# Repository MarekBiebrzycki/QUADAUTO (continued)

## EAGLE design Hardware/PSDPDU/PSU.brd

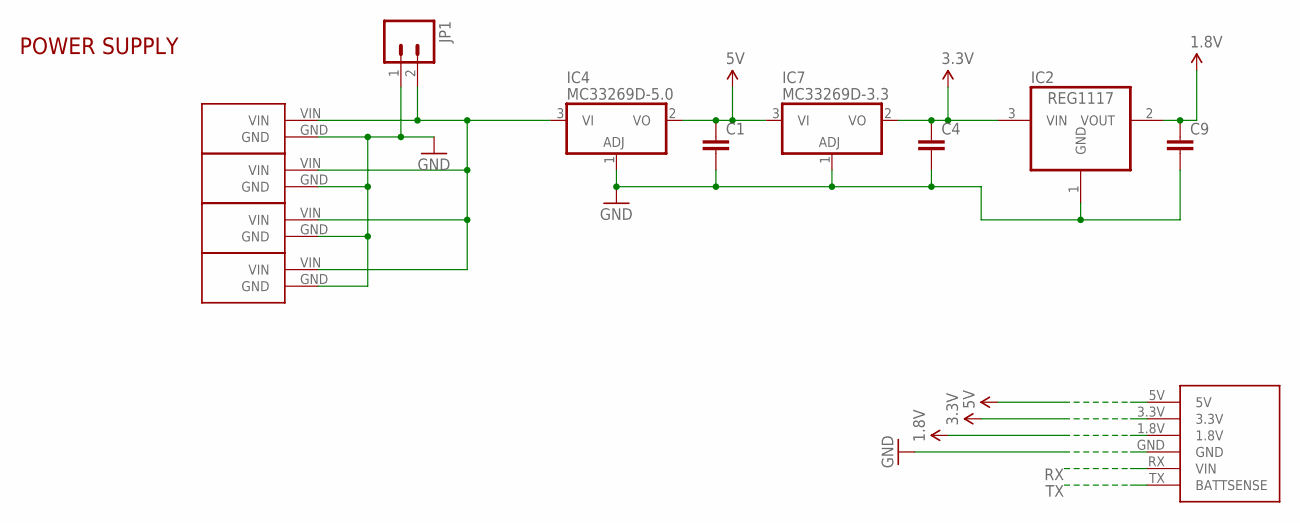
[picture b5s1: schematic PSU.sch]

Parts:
C1, C4, C9: CAP0805; 0805
IC2: REG1117; SOT223
IC4: MC33269D-5.0; DPACK
IC7: MC33269D-3.3; DPACK
JP1: M02PTH4; 1X02_XTRA_BIG
QB1: QUADBOARD
U$2, U$3, U$4, U$5: ESC_POWER; ESCPOWER

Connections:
1.8V: C9.1, IC2.2 (VOUT), QB1.1.8V
3.3V: C4.1, IC2.3 (VIN), IC7.2 (VO), QB1.3.3V
5V: C1.1, IC4.2 (VO), IC7.3 (VI), QB1.5V
GND: C1.2, C4.2, C9.2, IC2.1 (GND), IC4.1 (ADJ), IC7.1 (ADJ), JP1.1, QB1.GND, U$2.GND, U$3.GND, U$4.GND, U$5.GND
RX: QB1.RX (VIN)
TX: QB1.TX (BATTSENSE)
VIN: IC4.3 (VI), JP1.2, U$2.VIN, U$3.VIN, U$4.VIN, U$5.VIN

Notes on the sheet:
POWER SUPPLY

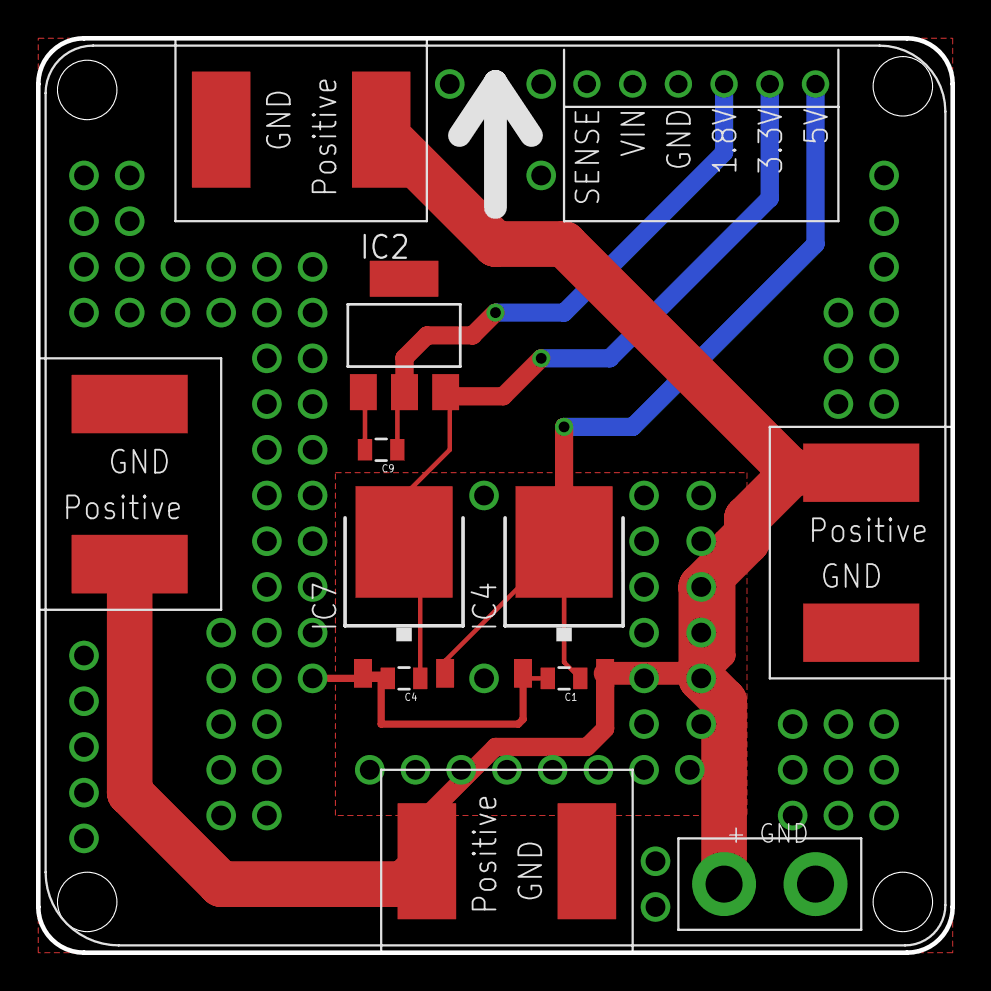
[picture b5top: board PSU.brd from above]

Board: 2 copper layers, 50.8 x 50.8 mm, 16 parts (0 on the bottom side), 5 nets.

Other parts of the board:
U$6, U$7, U$8, U$9: 5V; STAND-OFF

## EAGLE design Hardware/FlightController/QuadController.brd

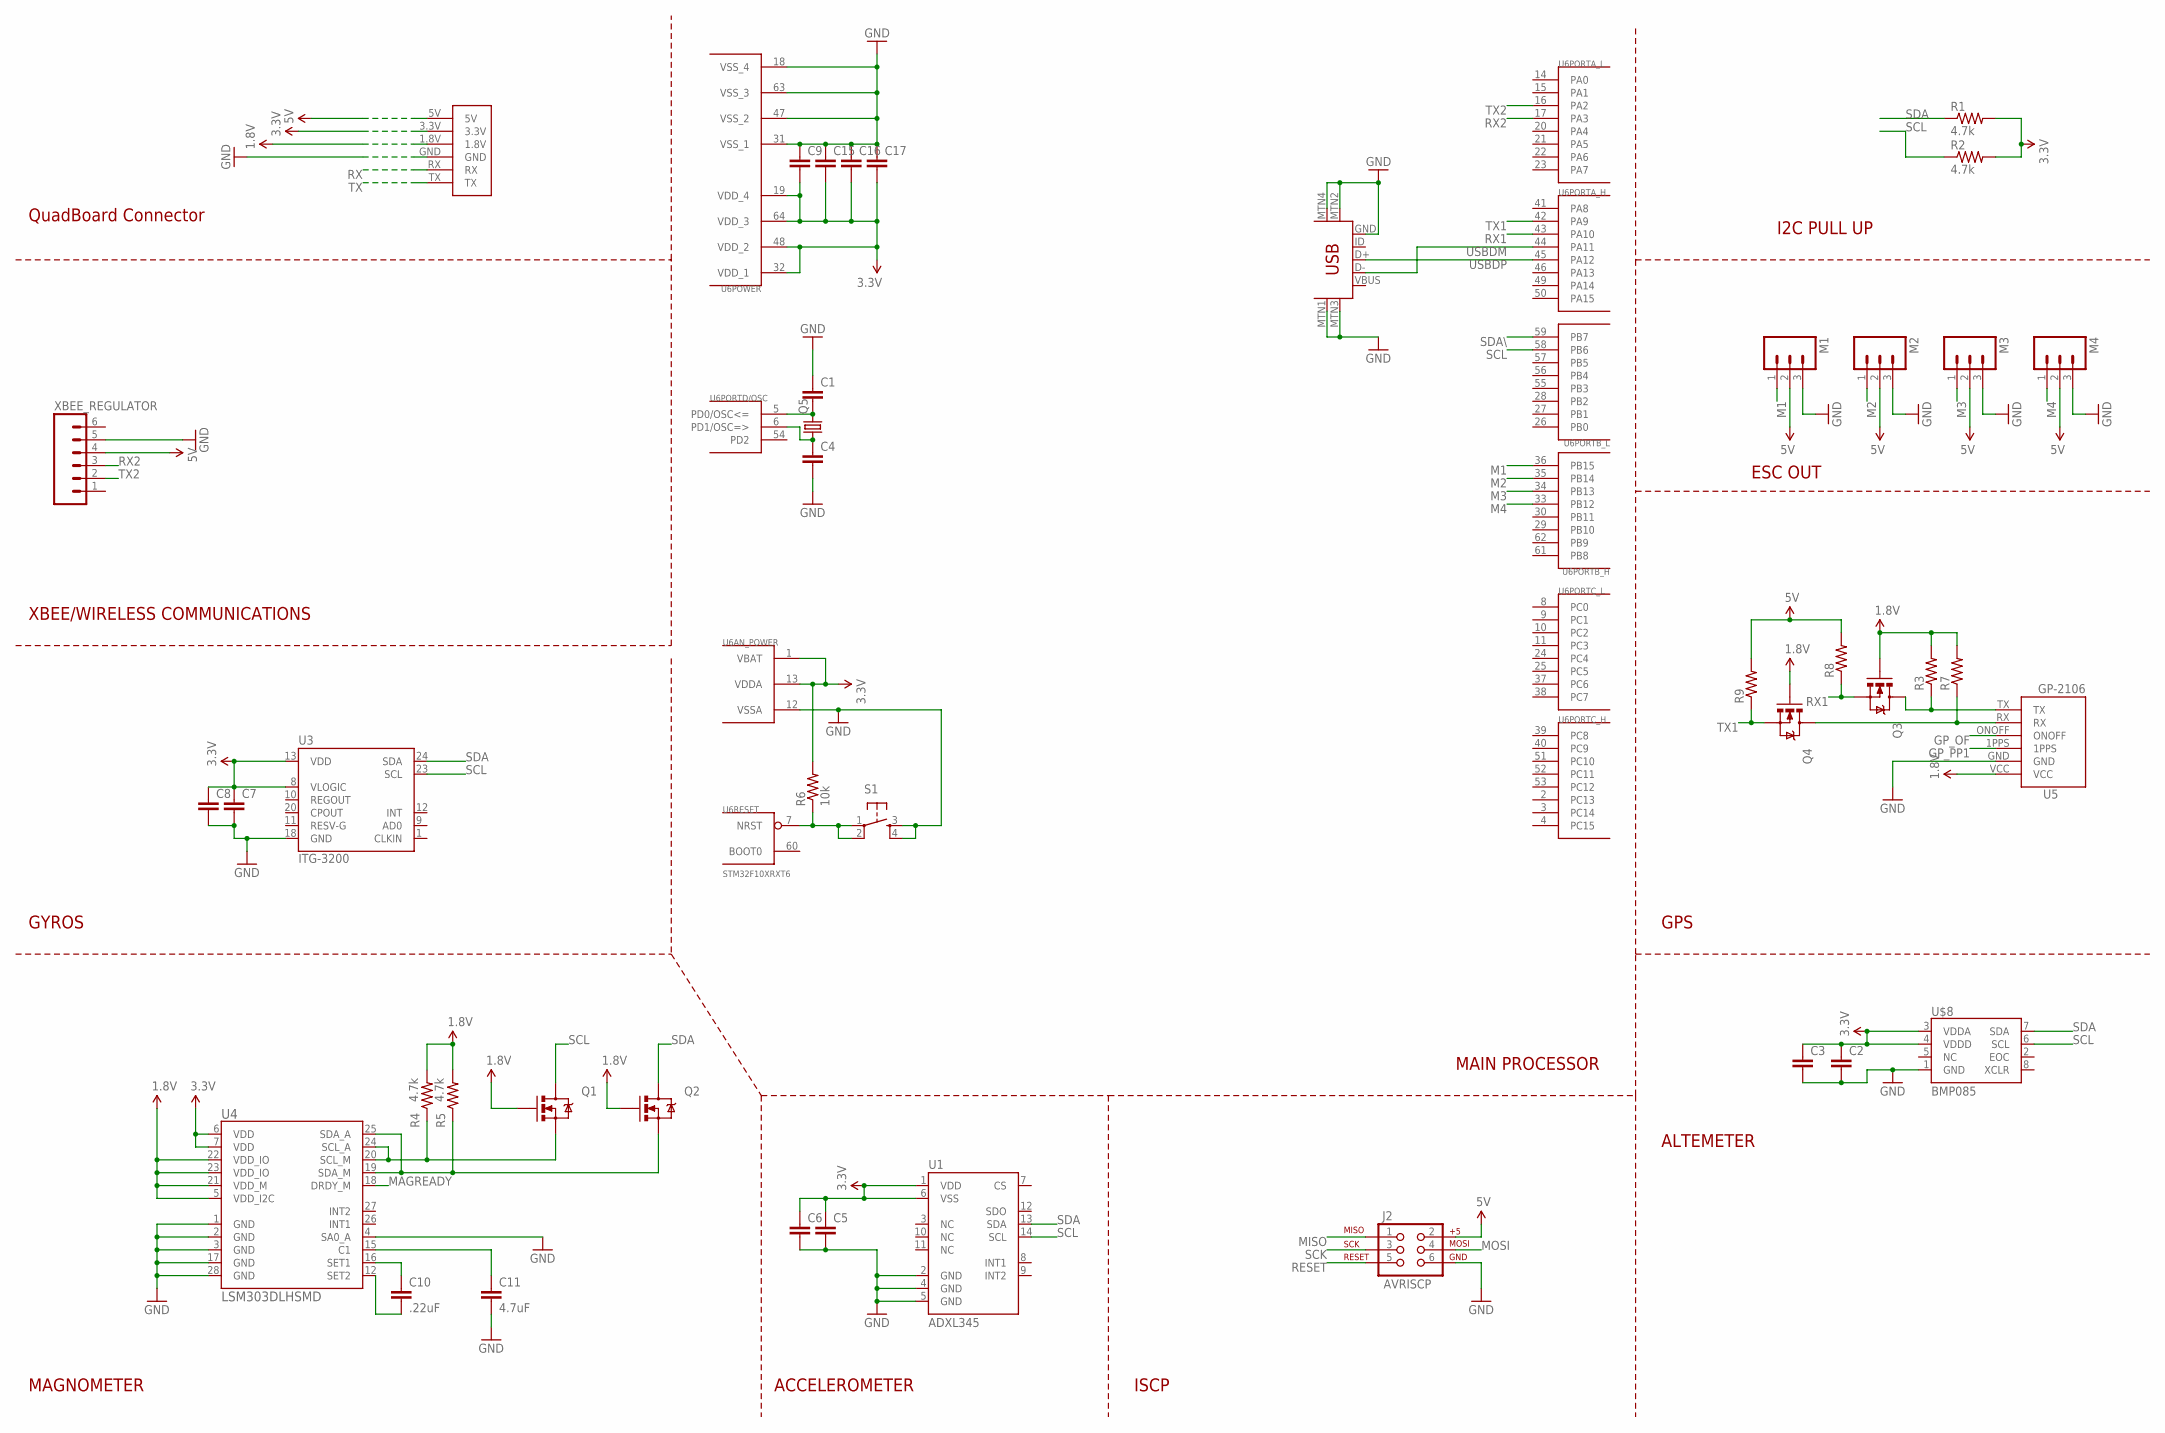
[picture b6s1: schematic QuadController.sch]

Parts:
C1, C2, C3, C4, C5, C6, C7, C8, C9, C15, C16, C17: CAP0805; 0805
C10: .22uF; 0805
C11: 4.7uF; 0805
J2: AVRISCP; 2X3
M1, M2, M3, M4: M03PTH; 1X03
Q1, Q2, Q3, Q4: MOSFET-NCHANNELSMD; SOT23-3
Q5: CRYSTALHC49UP; HC49UP
QB1: QUADBOARD
R1, R2, R4, R5: 4.7k; 0805
R3, R7, R8, R9: RESISTOR0805-RES; 0805
R6: 10k; 0805
S1: TAC_SWITCHSMD; TACTILE_SWITCH_SMD
U1: ADXL345; LGA14
U3: ITG-3200; QFN-24
U4: LSM303DLHSMD; LGA28-5X5
U5: GP-2106
U6: STM32F10XRXT6; TQFP64
U$1: USB-MINIB-5PIN; USB-MINIB
U$8: BMP085
XBEE_REGULATOR: M06SIP; 1X06

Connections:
1.8V: Q1.1 (G), Q2.1 (G), Q3.1 (G), Q4.1 (G), QB1.1.8V, R3.2, R4.2, R5.2, R7.2, U4.5 (VDD_I2C), U4.21 (VDD_M), U4.22 (VDD_IO), U4.23 (VDD_IO), U5.VCC
3.3V: C2.1, C3.1, C5.1, C6.1, C7.1, C8.1, C9.2, C15.2, C16.2, C17.2, QB1.3.3V, R1.2, R2.2, R6.2, U1.1 (VDD), U1.6 (VSS), U3.8 (VLOGIC), U3.13 (VDD), U4.6 (VDD), U4.7 (VDD), U6.1 (VBAT), U6.13 (VDDA), U6.19 (VDD_4), U6.32 (VDD_1), U6.48 (VDD_2), U6.64 (VDD_3), U$8.3 (VDDA), U$8.4 (VDDD)
5V: J2.2, M1.2, M2.2, M3.2, M4.2, QB1.5V, R8.2, R9.2, XBEE_REGULATOR.4
GND: C1.1, C2.2, C3.2, C4.2, C5.2, C6.2, C7.2, C8.2, C9.1, C11.2, C15.1, C16.1, C17.1, J2.6, M1.3, M2.3, M3.3, M4.3, QB1.GND, S1.3, S1.4, U1.2 (GND), U1.4 (GND), U1.5 (GND), U3.18 (GND), U4.1 (GND), U4.2 (GND), U4.3 (GND), U4.4 (SA0_A), U4.17 (GND), U4.28 (GND), U5.GND, U6.12 (VSSA), U6.18 (VSS_4), U6.31 (VSS_1), U6.47 (VSS_2), U6.63 (VSS_3), U$1.GND, U$1.MTN1 (MTN2), U$1.MTN2 (MTN3), U$1.MTN3 (MTN1), U$1.MTN4, U$8.1 (GND), XBEE_REGULATOR.5
GP_OF: U5.ONOFF
GP_PP1: U5.1PPS
M1: M1.1, U6.36 (PB15)
M2: M2.1, U6.35 (PB14)
M3: M3.1, U6.34 (PB13)
M4: M4.1, U6.33 (PB12)
MAGREADY: U4.18 (DRDY_M)
MISO: J2.1
MOSI: J2.4
unnamed: Q2.2 (S), R5.1, U4.19 (SDA_M), U4.25 (SDA_A)
unnamed: Q1.2 (S), R4.1, U4.20 (SCL_M), U4.24 (SCL_A)
unnamed: C11.1, U4.15 (C1)
unnamed: C10.1, U4.16 (SET1)
unnamed: Q3.3 (D), R3.1, U5.TX
unnamed: Q4.3 (D), R7.1, U5.RX
unnamed: C10.2, U4.12 (SET2)
unnamed: R6.1, S1.1, S1.2, U6.7 (NRST)
unnamed: C1.2, Q5.2, U6.5 (PD0/OSC<=)
unnamed: C4.1, Q5.1, U6.6 (PD1/OSC=>)
RESET: J2.5
RX: QB1.RX
RX1: Q3.2 (S), R8.1, U6.43 (PA10)
RX2: U6.17 (PA3), XBEE_REGULATOR.3
SCK: J2.3
SCL: Q1.3 (D), R2.1, U1.14 (SCL), U3.23 (SCL), U6.58 (PB6), U$8.6 (SCL)
SDA: Q2.3 (D), R1.1, U1.13 (SDA), U3.24 (SDA), U$8.7 (SDA)
SDA\: U6.59 (PB7)
TX: QB1.TX
TX1: Q4.2 (S), R9.1, U6.42 (PA9)
TX2: U6.16 (PA2), XBEE_REGULATOR.2
USBDM: U6.44 (PA11), U$1.D-
USBDP: U6.45 (PA12), U$1.D+

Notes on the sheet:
MAIN PROCESSOR
GYROS
MAGNOMETER
ACCELEROMETER
ALTEMETER
QuadBoard Connector
ESC OUT
I2C PULL UP
ISCP
GPS
XBEE/WIRELESS COMMUNICATIONS

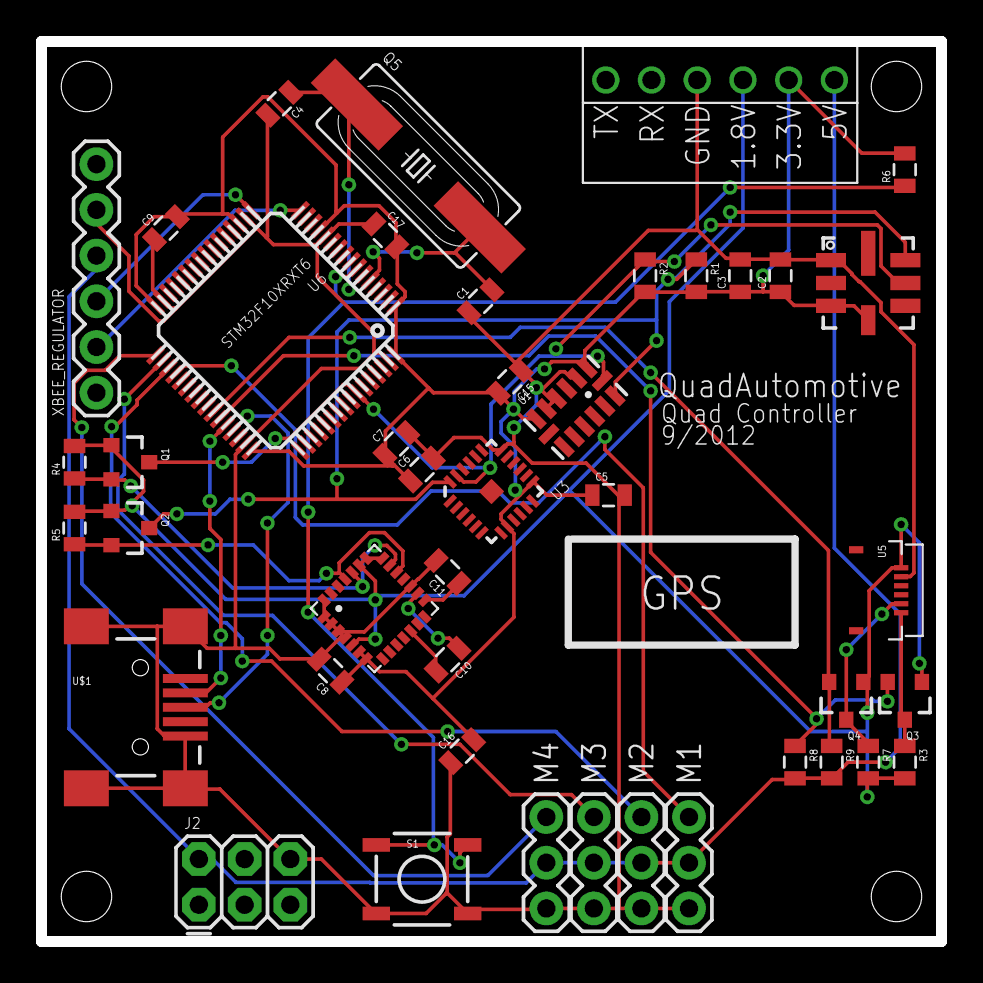
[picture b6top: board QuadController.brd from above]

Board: 2 copper layers, 50.0 x 50.0 mm, 43 parts (0 on the bottom side), 26 nets.

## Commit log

2012-09-24 Group Charter
2012-09-24 placeholders for folders and electronics boards
2012-09-26 added additional Charter Documents
2012-09-26 corrected communications doc
2012-11-03 Added Firmware
2012-11-03 Updated the Readme in the Firmware folder and added the libraries for the FlyMaple.
2012-11-03 Added Template Ground Control C# WPF ClaiburnMicro Project
2012-11-03 added a link to the readme on the Firmware
2012-11-03 updated the Main Readme
2012-11-03 added some of the GPS implementation to Navigation
